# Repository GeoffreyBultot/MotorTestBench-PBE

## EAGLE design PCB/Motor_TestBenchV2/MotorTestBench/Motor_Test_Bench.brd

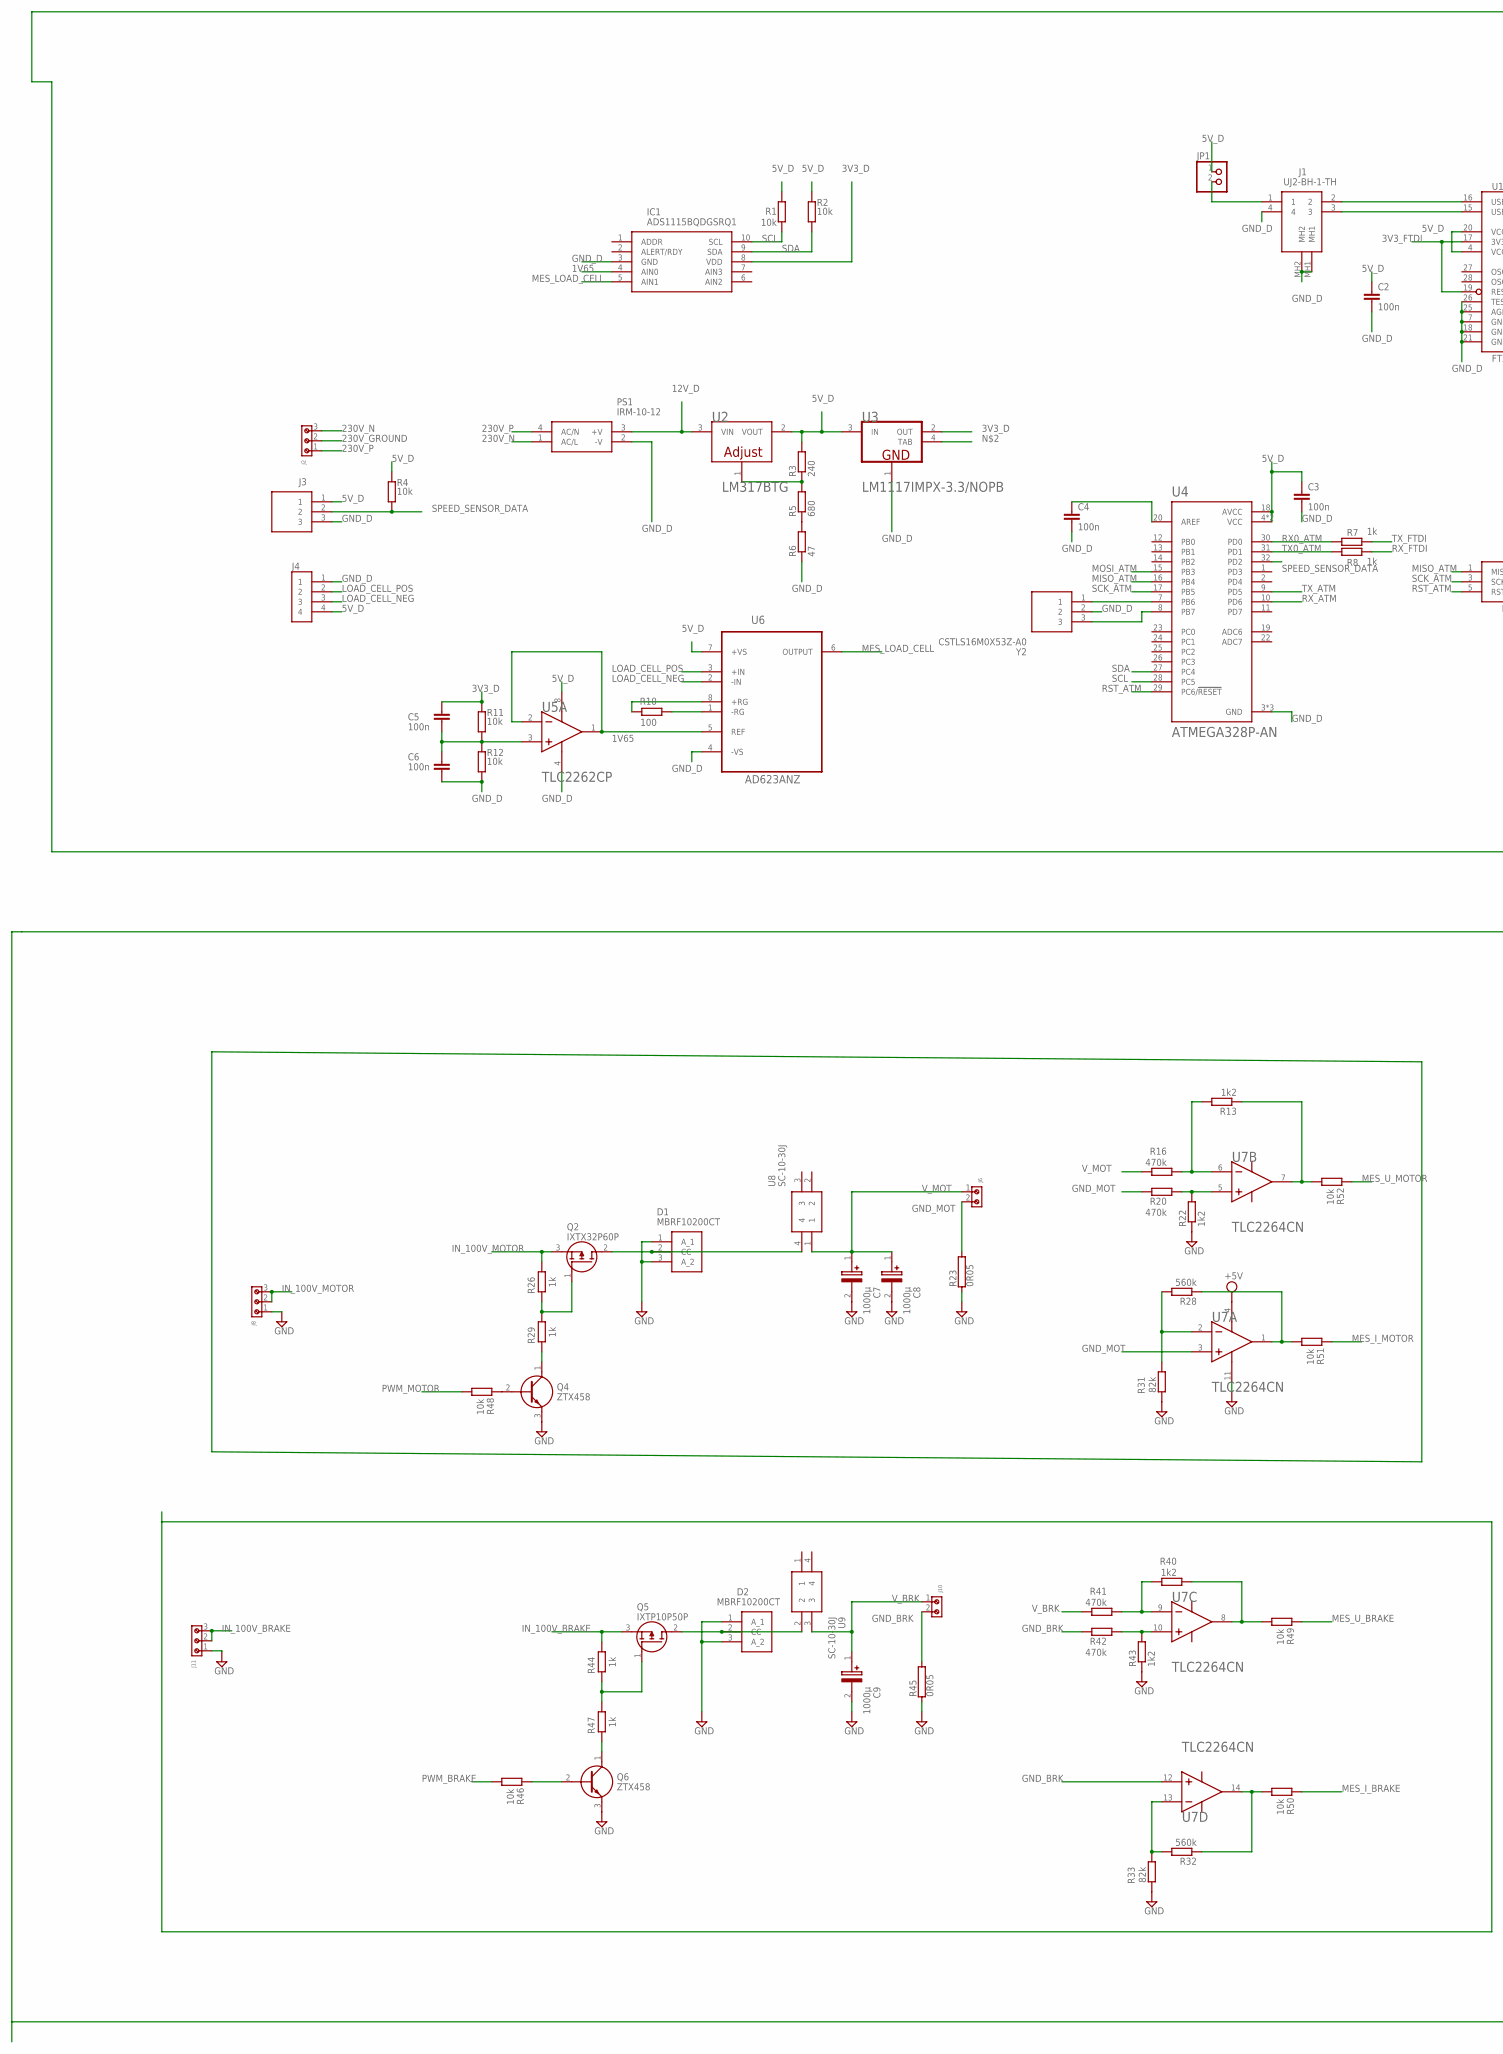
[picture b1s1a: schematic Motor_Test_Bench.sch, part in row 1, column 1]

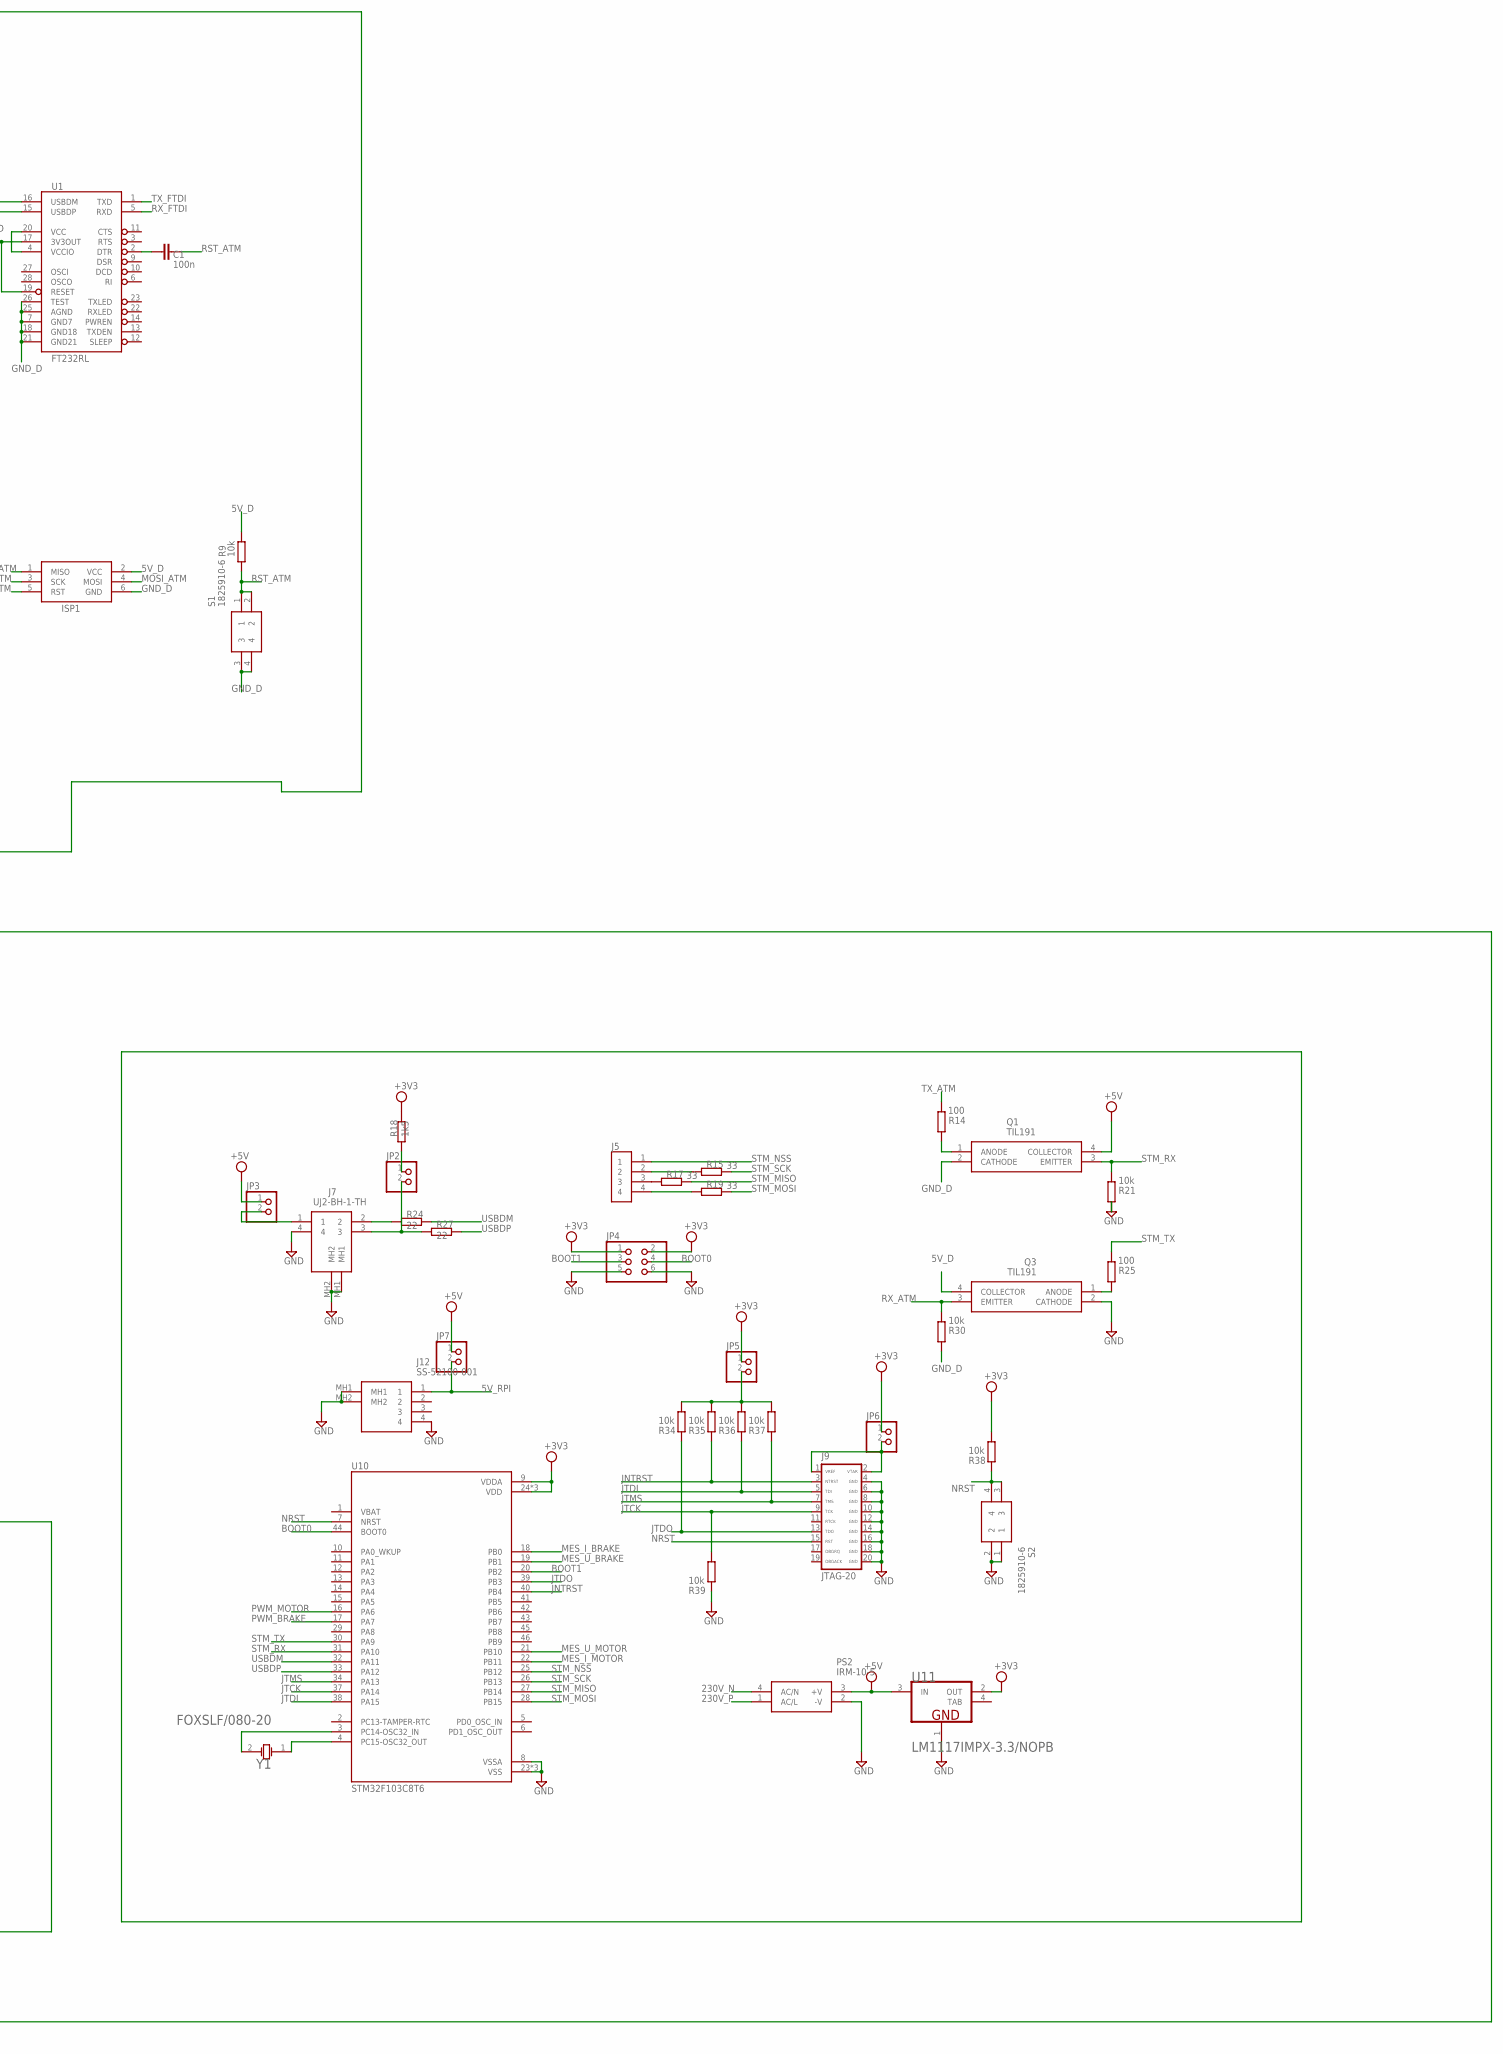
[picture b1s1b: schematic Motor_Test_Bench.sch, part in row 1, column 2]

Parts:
C1, C2, C3, C4: 100n; CAP_0805
C5, C6: 100n; C0805
C7, C8, C9: 1000µ; SLPX102M200C4P3
D1, D2: MBRF10200CT; TO254P490X1000X2143-3P
IC1: ADS1115BQDGSRQ1; SOP50P490X110-10N
ISP1: AVRISP-6; AVRISP
J1, J7: UJ2-BH-1-TH; UJ2BH1TH
J2, J8, J11: 691210910003
J3: B3B-XH-A(LF)(SN); SHDR3W64P0X250_1X3_990X575X700
J4, J5: B4B-XH-A(LF)(SN); JST_B4B-XH-A(LF)(SN)
J6, J10: 691210910002
J9: JTAG-20
J12: SS-52100-001; SS52100001
JP1, JP2, JP3, JP5, JP6, JP7: PINHD-1X2; 1X02
JP4: PINHD-2X3; 2X03
PS1: IRM-10-12; IRM-10
PS2: IRM-10-5; IRM-10
Q1, Q3: TIL191; DIP762W58P254L450H584Q4N
Q2: IXTX32P60P; TO545P521X1594X2566-3P
Q4, Q6: ZTX458
Q5: IXTP10P50P; TO254P483X1028X1700-3P
R1, R2, R4, R9, R11, R12, R21, R30, R38: 10k; R0805
R3: 240; R0805
R5: 680; R0805
R6: 47; R0805
R7, R8: 1k; R0805
R10, R14, R25: 100; R0805
R13, R22, R40, R43: 1k2; R0805
R15, R17, R19: 33; M0805
R16, R20, R41, R42: 470k; R0805
R18: 1k5; R0805
R23, R45: 0R05; RS05_69-70
R24, R27: 22; R0805
R26, R29, R44, R47: 1k; 0204/7
R28, R32: 560k; R0805
R31, R33: 82k; R0805
R34, R35, R36, R37, R39, R49, R50, R51, R52: 10k; M0805
R46, R48: 10k; 0204/7
S1, S2: 1825910-6
U1: FT232RL; SSOP28DB
U2: ON_SEMI_LM317BTGON_SEMI_LM317BTG_0_0; ON_SEMI_LM317BTG_0
U3, U11: NATIONAL_SEMICONDUCTOR_LM1117IMPX-3.3-NOPBNATIONA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; NATIONAL_SEMICONDUCTOR_LM1117IMPX-3.3-NOPB_2
U4: ATMEGA328P-AN; QFP80P900X900X120-32N
U5: TEXAS_INSTRUMENTS_TLC2262CPTEXAS_INSTRUMENTS_TLC2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; TEXAS_INSTRUMENTS_TLC2262CP_0
U6: AD623ANZ; DIP254P762X533-8
U7: TEXAS_INSTRUMENTS_TLC2264CNTEXAS_INSTRUMENTS_TLC2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; TEXAS_INSTRUMENTS_TLC2264CN_0
U8, U9: SC-10-30J
U10: STM32F103C8T6; QFP50P900X900X160-48N
Y1: FOX_ELECTRONICS_FOXSLF-080-20FOX_ELECTRONICS_FOXS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; FOX_ELECTRONICS_FOXSLF-080-20_0
Y2: CSTLS16M0X53Z-A0; CSTLS16M0X53ZA0

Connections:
1V65: IC1.4 (AIN0), U5.1 (OUT1), U5.2 (IN1-), U6.5 (REF)
3V3_D: C5.1, IC1.8 (VDD), R11.1, U3.2 (OUT)
3V3_FTDI: U1.17 (3V3OUT), U1.19 (RESET)
5V_D: C2.1, C3.1, ISP1.2 (VCC), J3.1, J4.4, JP1.1, Q3.4 (COLLECTOR), R1.2, R2.2, R3.2, R4.1, R9.2, U1.4 (VCCIO), U1.20 (VCC), U2.2 (VOUT), U3.3 (IN), U4.4 (VCC), U4.6 (VCC), U4.18 (AVCC), U5.8 (VDD+), U6.7 (+VS)
5V_RPI: J12.1, JP7.2
12V_D: PS1.3 (+V), U2.3 (VIN)
230V_GROUND: J2.2
230V_N: J2.3, PS1.1 (AC/L), PS2.4 (AC/N)
230V_P: J2.1, PS1.4 (AC/N), PS2.1 (AC/L)
+3V3: JP4.1, JP4.2, JP5.1, JP6.1, R18.1, R38.2, U10.9 (VDDA), U10.24 (VDD), U10.36 (VDD), U10.48 (VDD), U11.2 (OUT)
+5V: JP3.1, JP7.1, PS2.3 (+V), Q1.4 (COLLECTOR), U7.4 (VDD+), U11.3 (IN)
BOOT0: JP4.4, U10.44 (BOOT0)
BOOT1: JP4.3, U10.20 (PB2)
GND: C7.2 (-), C8.2 (-), C9.2 (-), D1.1 (A_1), D1.3 (A_2), D2.1 (A_1), D2.3 (A_2), J7.4, J7.MH1, J7.MH2, J8.1, J9.4 (GND), J9.6 (GND), J9.8 (GND), J9.10 (GND), J9.12 (GND), J9.14 (GND), J9.16 (GND), J9.18 (GND), J9.20 (GND), J11.1, J12.4, J12.MH1, J12.MH2, JP4.5, JP4.6, PS2.2 (-V), Q3.2 (CATHODE), Q4.3 (C), Q6.3 (C), R21.1, R22.1, R23.1, R31.2, R33.2, R39.1, R43.1, R45.1, S2.1, S2.2, U7.11 (VDD-/GND), U10.8 (VSSA), U10.23 (VSS), U10.35 (VSS), U10.47 (VSS), U11.1 (GND)
GND_BRK: J10.2, R42.2, R45.2, U7.12 (IN4+)
GND_D: C2.2, C3.2, C4.2, C6.2, IC1.3 (GND), ISP1.6 (GND), J1.4, J1.MH1, J1.MH2, J3.3, J4.1, PS1.2 (-V), Q1.2 (CATHODE), R6.1, R12.2, R30.1, S1.3, S1.4, U1.7 (GND7), U1.18 (GND18), U1.21 (GND21), U1.25 (AGND), U1.26 (TEST), U3.1 (GND), U4.3 (GND), U4.5 (GND), U4.21 (GND), U5.4 (VDD-/GND), U6.4 (-VS), Y2.2
GND_MOT: J6.2, R20.2, R23.2, U7.3 (IN1+)
IN_100V_BRAKE: J11.2, J11.3, Q5.3 (S), R44.2
IN_100V_MOTOR: J8.2, J8.3, Q2.3 (S), R26.2
JNTRST: J9.3 (NTRST), R35.1, U10.40 (PB4)
JTCK: J9.9 (TCK), R39.2, U10.37 (PA14)
JTDI: J9.5 (TDI), R36.1, U10.38 (PA15)
JTDO: J9.13 (TDO), R34.1, U10.39 (PB3)
JTMS: J9.7 (TMS), R37.1, U10.34 (PA13)
LOAD_CELL_NEG: J4.3, U6.2 (-IN)
LOAD_CELL_POS: J4.2, U6.3 (+IN)
MES_I_BRAKE: R50.1, U10.18 (PB0)
MES_I_MOTOR: R51.1, U10.22 (PB11)
MES_LOAD_CELL: IC1.5 (AIN1), U6.6 (OUTPUT)
MES_U_BRAKE: R49.1, U10.19 (PB1)
MES_U_MOTOR: R52.1, U10.21 (PB10)
MISO_ATM: ISP1.1 (MISO), U4.16 (PB4)
MOSI_ATM: ISP1.4 (MOSI), U4.15 (PB3)
unnamed: D1.2 (CC), Q2.2 (D), U8.4
unnamed: R5.1, R6.2
unnamed: R3.1, R5.2, U2.1 (ADJUST)
unnamed: J7.2, R24.2
unnamed: J7.3, JP2.2, R27.2
unnamed: JP2.1, R18.2
unnamed: R28.2, R31.1, U7.2 (IN1-)
unnamed: Q2.1 (G), R26.1, R29.2
unnamed: Q4.1 (E), R29.1
unnamed: R13.2, R16.1, U7.6 (IN2-)
unnamed: R20.1, R22.2, U7.5 (IN2+)
unnamed: C1.2, U1.2 (DTR)
unnamed: C4.1, U4.20 (AREF)
unnamed: Q5.1 (G), R44.1, R47.2
unnamed: R32.2, R33.1, U7.13 (IN4-)
unnamed: Q6.2 (B), R46.1
unnamed: R42.1, R43.2, U7.10 (IN3+)
unnamed: R40.2, R41.1, U7.9 (IN3-)
unnamed: Q4.2 (B), R48.1
unnamed: Q6.1 (E), R47.1
unnamed: R28.1, R51.2, U7.1 (OUT1)
unnamed: J1.2, U1.16 (USBDM)
unnamed: R10.2, U6.1 (-RG)
unnamed: C5.2, C6.1, R11.2, R12.1, U5.3 (IN1+)
unnamed: R10.1, U6.8 (+RG)
unnamed: J1.3, U1.15 (USBDP)
unnamed: D2.2 (CC), Q5.2 (D), U9.2
unnamed: Q1.1 (ANODE), R14.1
unnamed: Q3.1 (ANODE), R25.1
unnamed: J7.1, JP3.2
unnamed: J9.1 (VREF), J9.2 (VTAR), JP6.2
unnamed: JP5.2, R34.2, R35.2, R36.2, R37.2
unnamed: J1.1, JP1.2
unnamed: J5.2, R15.2
unnamed: J5.3, R17.2
unnamed: J5.4, R19.2
unnamed: U10.4 (PC15-OSC32_OUT), Y1.1
unnamed: U10.3 (PC14-OSC32_IN), Y1.2
unnamed: R32.1, R50.2, U7.14 (OUT4)
unnamed: R40.1, R49.2, U7.8 (OUT3)
unnamed: R13.1, R52.2, U7.7 (OUT2)
unnamed: U4.7 (PB6), Y2.1
unnamed: U4.8 (PB7), Y2.3
NRST: J9.15 (RST), R38.1, S2.3, S2.4, U10.7 (NRST)
PWM_BRAKE: R46.2, U10.17 (PA7)
PWM_MOTOR: R48.2, U10.16 (PA6)
RST_ATM: C1.1, ISP1.5 (RST), R9.1, S1.1, S1.2, U4.29 (PC6/!RESET)
RX0_ATM: R7.1, U4.30 (PD0)
RX_ATM: Q3.3 (EMITTER), R30.2, U4.10 (PD6)
RX_FTDI: R8.2, U1.5 (RXD)
SCK_ATM: ISP1.3 (SCK), U4.17 (PB5)
SCL: IC1.10 (SCL), R1.1, U4.28 (PC5)
SDA: IC1.9 (SDA), R2.1, U4.27 (PC4)
SPEED_SENSOR_DATA: J3.2, R4.2, U4.32 (PD2)
STM_MISO: R17.1, U10.27 (PB14)
STM_MOSI: R19.1, U10.28 (PB15)
STM_NSS: J5.1, U10.25 (PB12)
STM_RX: Q1.3 (EMITTER), R21.2, U10.31 (PA10)
STM_SCK: R15.1, U10.26 (PB13)
STM_TX: R25.2, U10.30 (PA9)
TAB: U11.4 (TAB)
TX0_ATM: R8.1, U4.31 (PD1)
TX_ATM: R14.2, U4.9 (PD5)
TX_FTDI: R7.2, U1.1 (TXD)
USBDM: R24.1, U10.32 (PA11)
USBDP: R27.1, U10.33 (PA12)
V_BRK: C9.1 (+), J10.1, R41.2, U9.3
V_MOT: C7.1 (+), C8.1 (+), J6.1, R16.2, U8.1

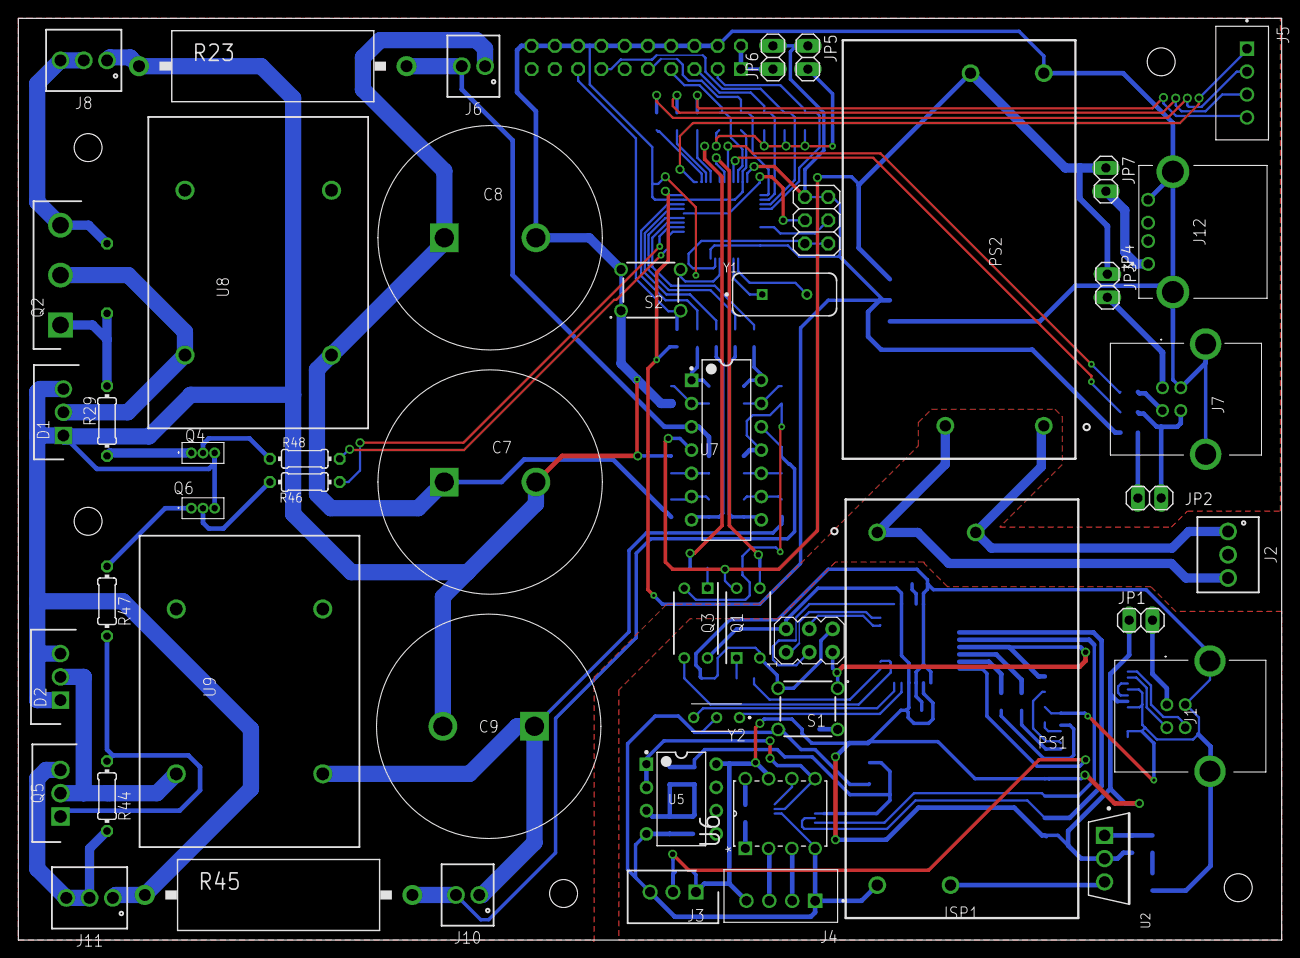
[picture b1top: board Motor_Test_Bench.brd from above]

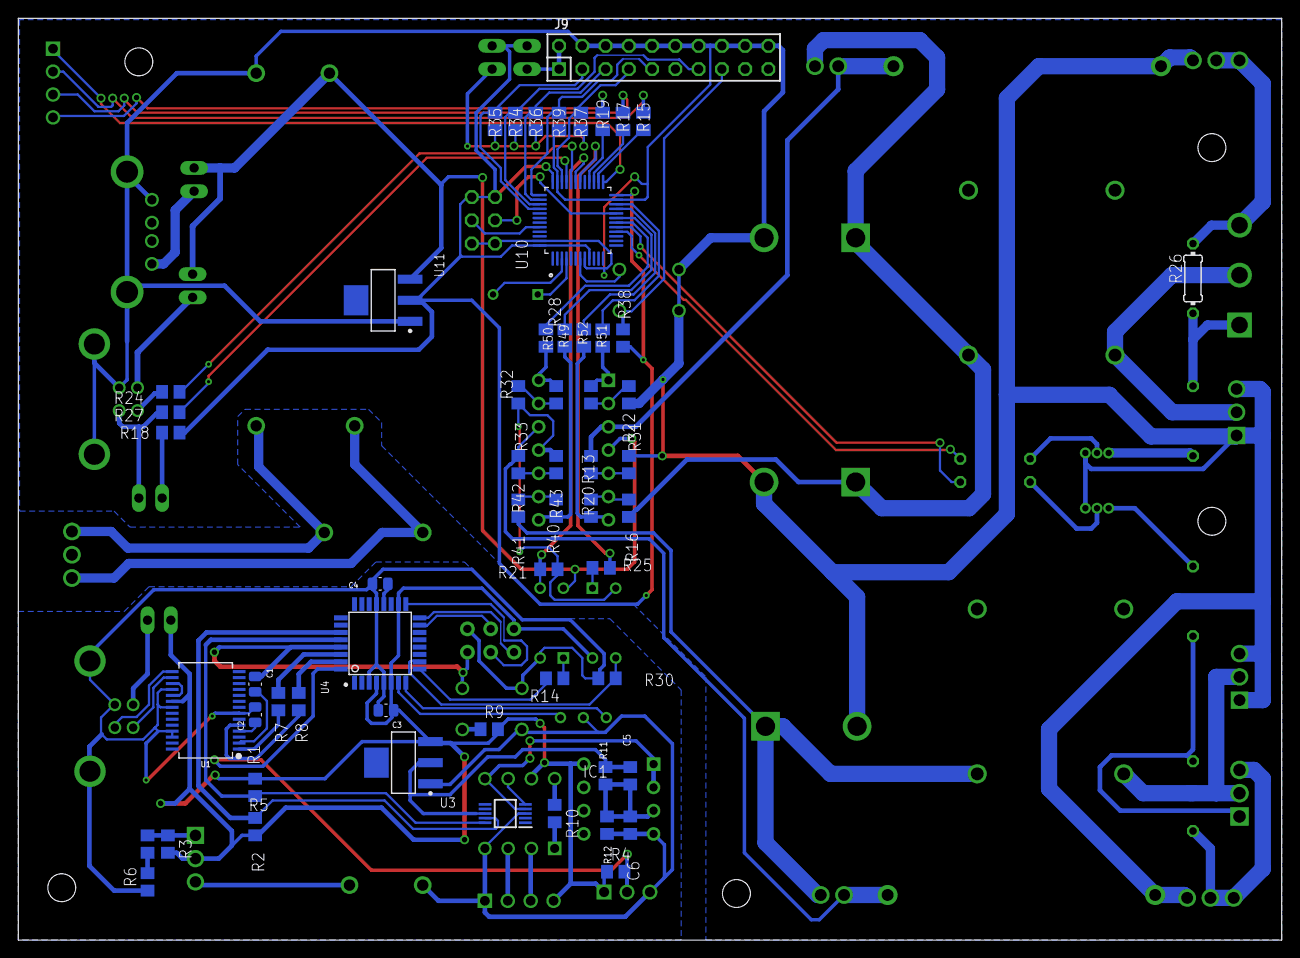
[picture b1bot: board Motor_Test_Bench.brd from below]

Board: 2 copper layers, 137.9 x 100.6 mm, 107 parts (58 on the bottom side), 99 nets.

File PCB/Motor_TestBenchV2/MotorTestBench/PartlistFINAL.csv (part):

Partlist

Exported from Motor_Test_Bench.brd at 05-06-20 10:19

EAGLE Version 9.5.0 Copyright (c) 1988-2019 Autodesk, Inc.

Assembly variant: 

Part     Value                                                                                    Package                                      Library                                   Position (mil)        Orientation

C1       100n                                                                                     CAP_0805                                     Resistor_Capacitor                        (4331.25 1093.75)     MR270
C2       100n                                                                                     CAP_0805                                     Resistor_Capacitor                        (4331.25 962.5)       MR90
C3       100n                                                                                     CAP_0805                                     Resistor_Capacitor                        (3768.75 981.25)      MR180
C4       100n                                                                                     CAP_0805                                     Resistor_Capacitor                        (3793.75 1525)        MR180
C5       100n                                                                                     C0805                                        resistor                                  (2718.75 700)         MR270
C6       100n                                                                                     C0805                                        resistor                                  (2718.75 487.5)       MR270
C7       1000µ                                                                                    SLPX102M200C4P3                              SamacSys_Parts                            (1750 1962.5)         R0
C8       1000µ                                                                                    SLPX102M200C4P3                              SamacSys_Parts                            (1750 3012.5)         R0
C9       1000µ                                                                                    SLPX102M200C4P3                              SamacSys_Parts                            (2137.5 912.5)        R180
D1       MBRF10200CT                                                                              TO254P490X1000X2143-3P                       SamacSys_Parts                            (112.5 2162.5)        R90
D2       MBRF10200CT                                                                              TO254P490X1000X2143-3P                       SamacSys_Parts                            (100 1025)            R90
IC1      ADS1115BQDGSRQ1                                                                          SOP50P490X110-10N                            SamacSys_Parts                            (3256.25 537.5)       MR180
ISP1     AVRISP-6                                                                                 AVRISP                                       adafruit                                  (3318.75 1281.25)     R90
J1       UJ2-BH-1-TH                                                                              UJ2BH1TH                                     SamacSys_Parts                            (5281.25 956.25)      R90
J2                                                                                                691210910003                                 Wurth_Connectors_WR-TBL Rising Cage Clamp (5118.75 1650)        R270
J3       B3B-XH-A(LF)(SN)                                                                         SHDR3W64P0X250_1X3_990X575X700               SamacSys_Parts                            (2831.25 200)         R180
J4       B4B-XH-A(LF)(SN)                                                                         JST_B4B-XH-A(LF)(SN)                         B4B-XH-A_LF__SN_                          (3343.75 162.5)       R180
J5       B4B-XH-A(LF)(SN)                                                                         JST_B4B-XH-A(LF)(SN)                         B4B-XH-A_LF__SN_                          (5200 3825)           R270
J6                                                                                                691210910002                                 Wurth_Connectors_WR-TBL Rising Cage Clamp (1875 3750)           R180
J7       UJ2-BH-1-TH                                                                              UJ2BH1TH                                     SamacSys_Parts                            (5262.5 2318.75)      R90
J8                                                                                                691210910003                                 Wurth_Connectors_WR-TBL Rising Cage Clamp (200 3775)            R180
J9       JTAG-20                                                                                  JTAG-20                                      luminary-arm                              (2575 3787.5)         MR0
J10                                                                                               691210910002                                 Wurth_Connectors_WR-TBL Rising Cage Clamp (1850 187.5)          R180
J11                                                                                               691210910003                                 Wurth_Connectors_WR-TBL Rising Cage Clamp (225 175)             R180
J12      SS-52100-001                                                                             SS52100001                                   SamacSys_Parts                            (4775 2900)           R90
JP1                                                                                               1X02                                         DC_LOAD_AU                                (4743.75 1368.75)     R0
JP2                                                                                               1X02                                         DC_LOAD_AU                                (4781.25 1893.75)     R0
JP3                                                                                               1X02                                         DC_LOAD_AU                                (4600 2806.25)        R270
JP4                                                                                               2X03                                         pinhead                                   (3350 3087.5)         R270
JP5                                                                                               1X02                                         DC_LOAD_AU                                (3312.5 3787.5)       R270
JP6                                                                                               1X02                                         DC_LOAD_AU                                (3162.5 3787.5)       R270
JP7                                                                                               1X02                                         DC_LOAD_AU                                (4593.75 3262.5)      R270
PS1      IRM-10-12                                                                                IRM-10                                       SamacSys_Parts                            (3475 1887.5)         R270
PS2      IRM-10-5                                                                                 IRM-10                                       SamacSys_Parts                            (4462.5 2062.5)       R90
Q1       TIL191                                                                                   DIP762W58P254L450H584Q4N                     SamacSys_Parts                            (3056.25 1356.25)     R90
Q2       IXTX32P60P                                                                               TO545P521X1594X2566-3P                       SamacSys_Parts                            (100 2637.5)          R90
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

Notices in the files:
parts and their libraries:
Wurth_Connectors_WR-TBL Rising Cage Clam: Copyright: Würth Elektronik
luminary-arm: Copyright (C) 2008, Bob Starr
SparkFun-IC-Comms: Licensing: Creative Commons ShareAlike 4.0 International - https://creativecommons.org/licenses/by-sa/4.0
